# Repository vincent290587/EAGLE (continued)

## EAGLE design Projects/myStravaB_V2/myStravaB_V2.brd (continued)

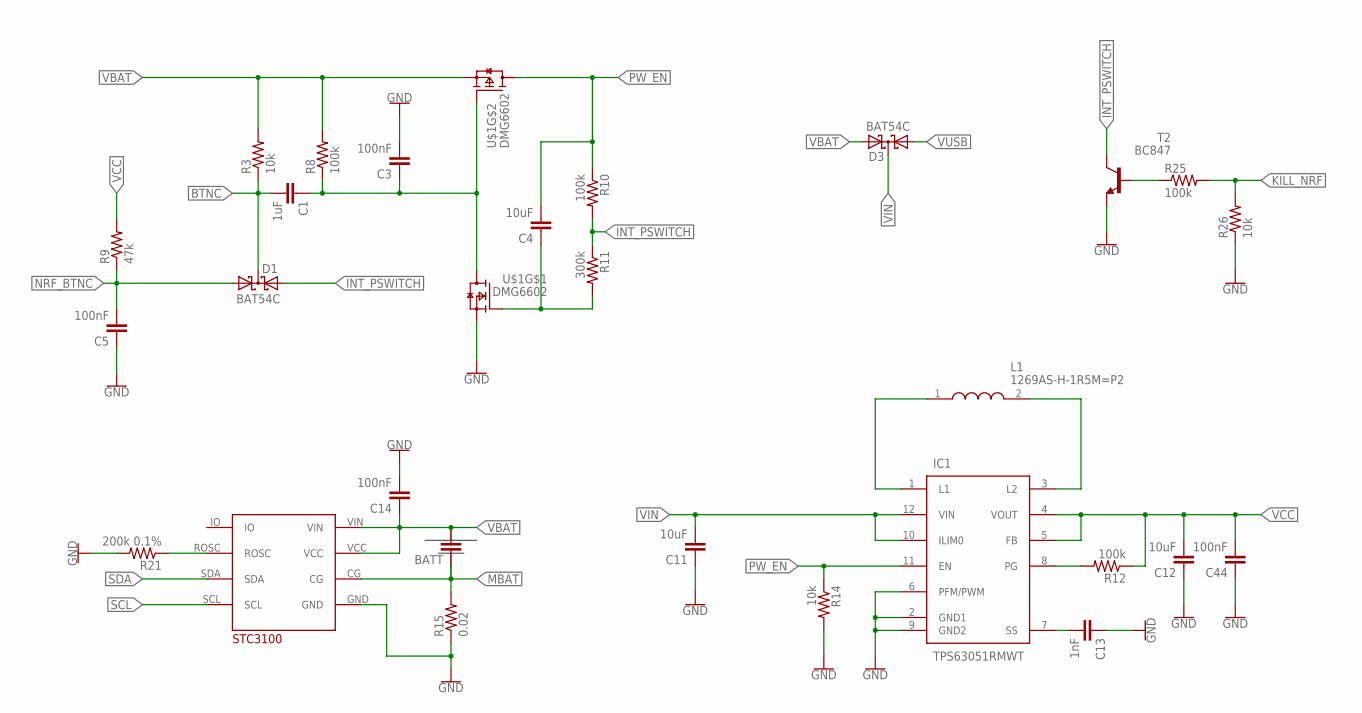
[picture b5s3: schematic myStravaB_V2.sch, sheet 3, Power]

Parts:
BATT: C-EUC1210; C1210
C1: 1uF; 0603
C3, C5: 100nF; 0603
C4: 10uF; 0603
C11: 10uF; C0805
C12: 10uF; C0603
C13: 1nF; C0603
C14, C44: 100nF; C0603
D1, D3: BAT54C; SOT23
IC1: TPS63051RMWT; QFN50P250X250X100-12N
L1: 1269AS-H-1R5M=P2; INDC2520X110N
R3, R14, R26: 10k; R0603
R8, R10, R12, R25: 100k; R0603
R9: 47k; R0603
R11: 300k; R0603
R15: 0.02; R0603
R21: 200k 0.1%; R0603
T2: BC847; SOT23
U$1: DMG6602; TSOT26
U$6: STC3100

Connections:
BTNC: C1.2, D1.3 (CC), R3.1; also elsewhere on the board
GND: C3.2, C5.1, C11.1, C12.1, C13.1, C14.2, C44.1, IC1.2 (GND1), IC1.6 (PFM/PWM), IC1.9 (GND2), R14.2, R15.1, R21.2, R26.1, T2.2 (E), U$1.P$5 (S), U$6.GND; also elsewhere on the board
INT_PSWITCH: D1.2 (A2), R10.2, R11.1, T2.3 (C)
KILL_NRF: R25.2, R26.2; also elsewhere on the board
L1: IC1.1 (L1), L1.1
L2: IC1.3 (L2), L1.2
MBAT: BATT.1, R15.2, U$6.CG
unnamed: C1.1, C3.1, R8.1, U$1.P$3 (G), U$1.P$6 (D)
unnamed: R25.1, T2.1 (B)
unnamed: C4.1, R11.2, U$1.P$1 (G)
NRF_BTNC: C5.2, D1.1 (A1), R9.1; also elsewhere on the board
PG: IC1.8 (PG), R12.2
PW_EN: C4.2, IC1.11 (EN), R10.1, R14.1, U$1.P$4 (D); also elsewhere on the board
ROSC: R21.1, U$6.ROSC
SCL: U$6.SCL; also elsewhere on the board
SDA: U$6.SDA; also elsewhere on the board
SS: C13.2, IC1.7 (SS)
VBAT: BATT.2, C14.1, D3.2 (A2), R3.2, R8.2, U$1.P$2 (S), U$6.VCC, U$6.VIN; also elsewhere on the board
VCC: C12.2, C44.2, IC1.4 (VOUT), IC1.5 (FB), R9.2, R12.1; also elsewhere on the board
VIN: C11.2, D3.3 (CC), IC1.10 (ILIM0), IC1.12 (VIN)
VUSB: D3.1 (A1); also elsewhere on the board

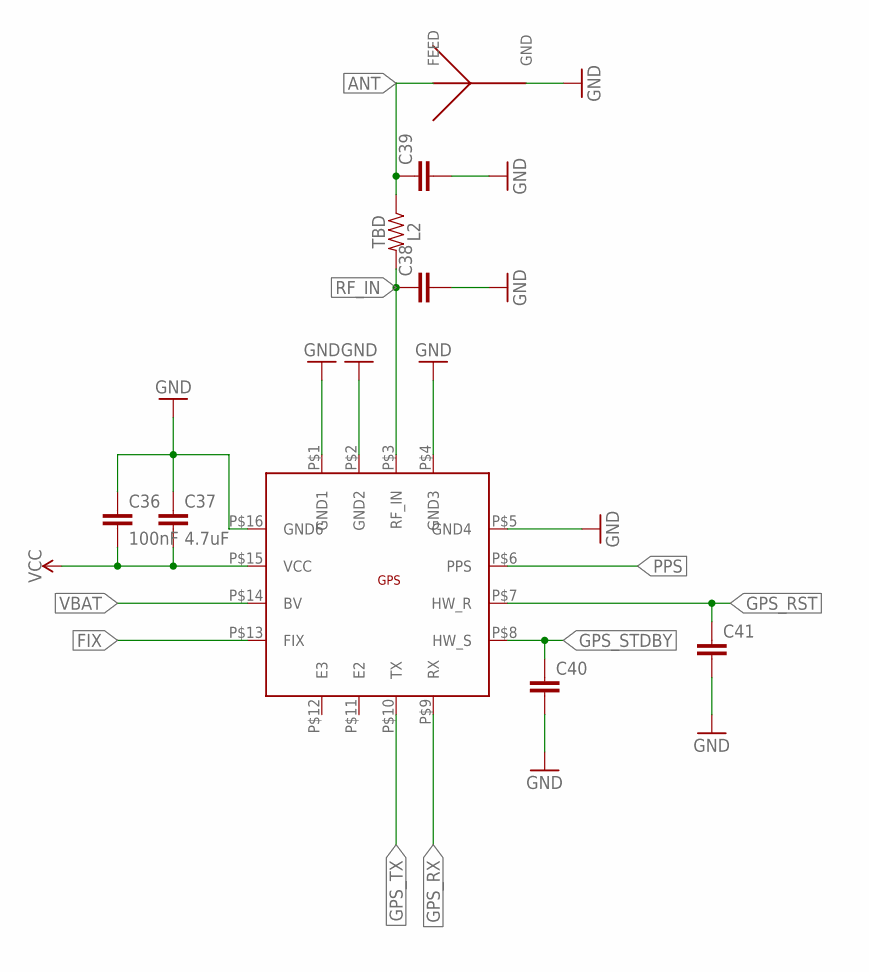
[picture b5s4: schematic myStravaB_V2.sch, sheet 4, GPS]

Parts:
C36: 100nF; C0603
C37: 4.7uF; C0603
C38, C39, C40, C41: C-EUC0603; C0603
L2: TBD; 0603
U$4: SR4G008
U$5: M10578

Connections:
ANT: C39.1, L2.1, U$4.P$2 (FEED)
FIX: U$5.P$13 (FIX); also elsewhere on the board
GND: C36.1, C37.1, C38.2, C39.2, C40.2, C41.2, U$4.P$3 (GND), U$4.P$4 (GND), U$4.P$6 (GND), U$5.P$1 (GND1), U$5.P$2 (GND2), U$5.P$4 (GND3), U$5.P$5 (GND4), U$5.P$16 (GND6); also elsewhere on the board
GPS_RST: C41.1, U$5.P$7 (HW_R); also elsewhere on the board
GPS_RX: U$5.P$9 (RX); also elsewhere on the board
GPS_STDBY: C40.1, U$5.P$8 (HW_S); also elsewhere on the board
GPS_TX: U$5.P$10 (TX); also elsewhere on the board
PPS: U$5.P$6 (PPS)
RF_IN: C38.1, L2.2, U$5.P$3 (RF_IN)
VBAT: U$5.P$14 (BV); also elsewhere on the board
VCC: C36.2, C37.2, U$5.P$15 (VCC); also elsewhere on the board

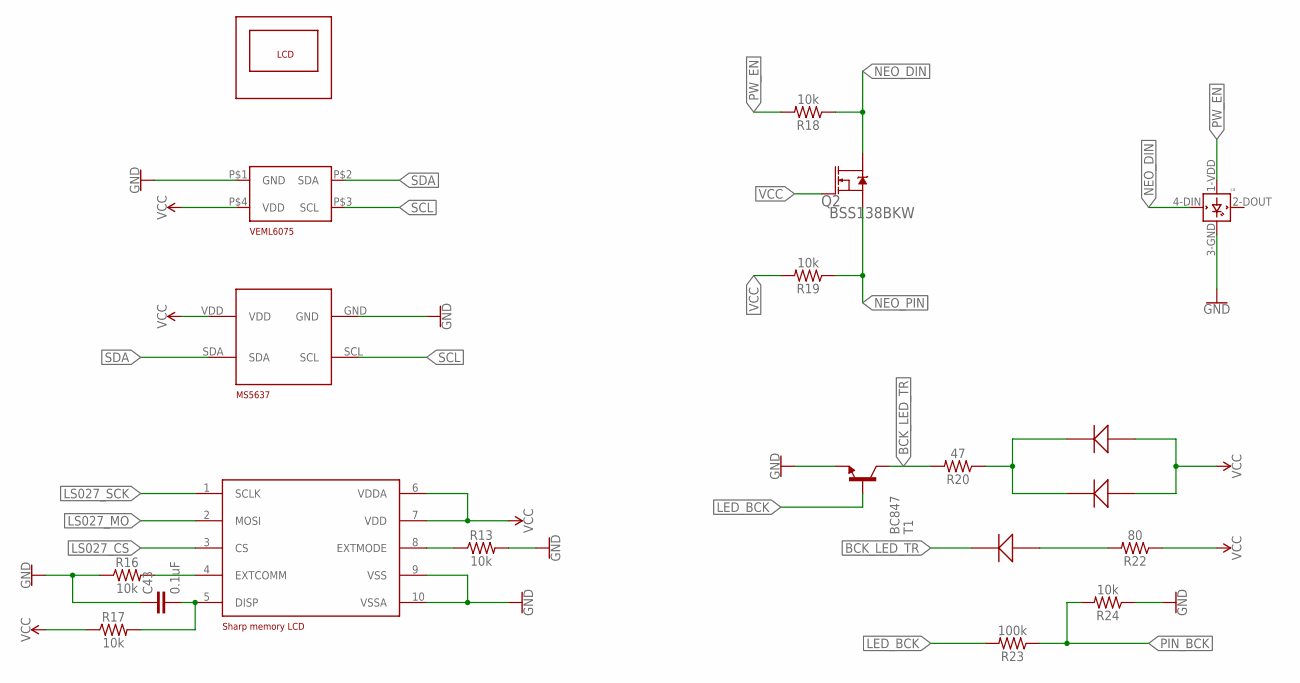
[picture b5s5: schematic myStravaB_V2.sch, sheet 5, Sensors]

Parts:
C43: 0.1uF; 0603
L4: WS2812B
MS1: MS5637
Q2: BSS138BKW; SOT65P210X110-3N
R13, R16, R17, R18, R19, R24: 10k; 0603
R20: 47; 0603
R22: 80; 0603
R23: 100k; 0603
T1: BC847; SOT23
U$14: VEML6075
U$15: SHARP27_FOOTPRINT; LCD27
U$16: SHARP27
U$17, U$18, U$19: KPA-2106SECK

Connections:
BCK_LED_TR: R20.2, T1.3 (C), U$19.P$1
DISP1: C43.2, R17.2, U$16.5 (DISP)
EXTCOMM1: R16.2, U$16.4 (EXTCOMM)
EXTMODE1: R13.1, U$16.8 (EXTMODE)
GND: C43.1, L4.3-GND (GND), MS1.GND, R13.2, R16.1, R24.1, T1.2 (E), U$14.P$1 (GND), U$16.9 (VSS), U$16.10 (VSSA); also elsewhere on the board
LED_BCK: R23.2, T1.1 (B)
LS027_CS: U$16.3 (CS); also elsewhere on the board
LS027_MO: U$16.2 (MOSI); also elsewhere on the board
LS027_SCK: U$16.1 (SCLK); also elsewhere on the board
unnamed: R22.2, U$19.P$2
unnamed: R20.1, U$17.P$1, U$18.P$1
NEO_DIN: L4.4-DIN (DIN), Q2.3 (D), R18.1
NEO_PIN: Q2.2 (S), R19.1; also elsewhere on the board
PIN_BCK: R23.1, R24.2
PW_EN: L4.1-VDD (VDD), R18.2; also elsewhere on the board
SCL: MS1.SCL, U$14.P$3 (SCL); also elsewhere on the board
SDA: MS1.SDA, U$14.P$2 (SDA); also elsewhere on the board
VCC: MS1.VDD, Q2.1 (G), R17.1, R19.2, R22.1, U$14.P$4 (VDD), U$16.6 (VDDA), U$16.7 (VDD), U$17.P$2, U$18.P$2; also elsewhere on the board

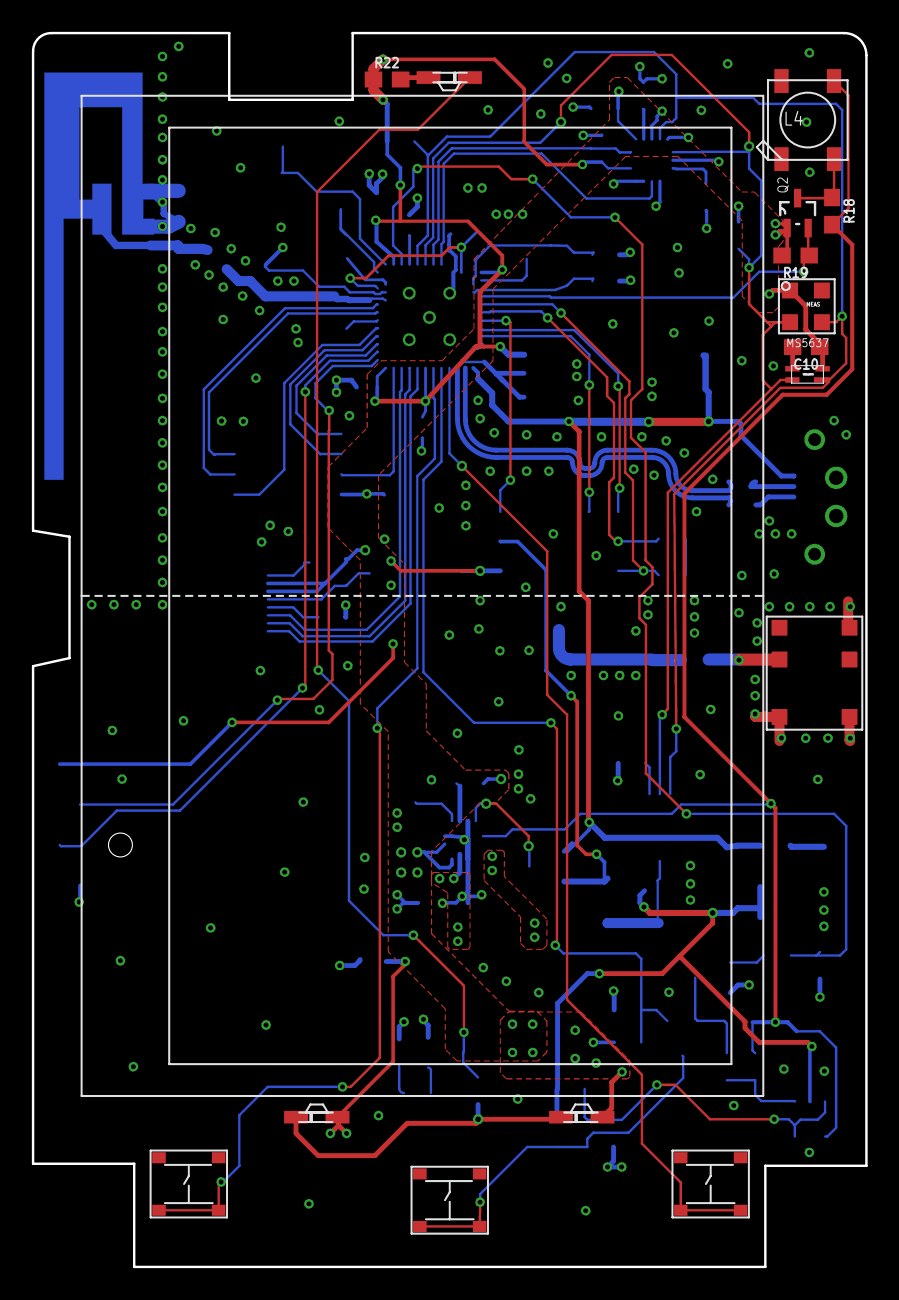
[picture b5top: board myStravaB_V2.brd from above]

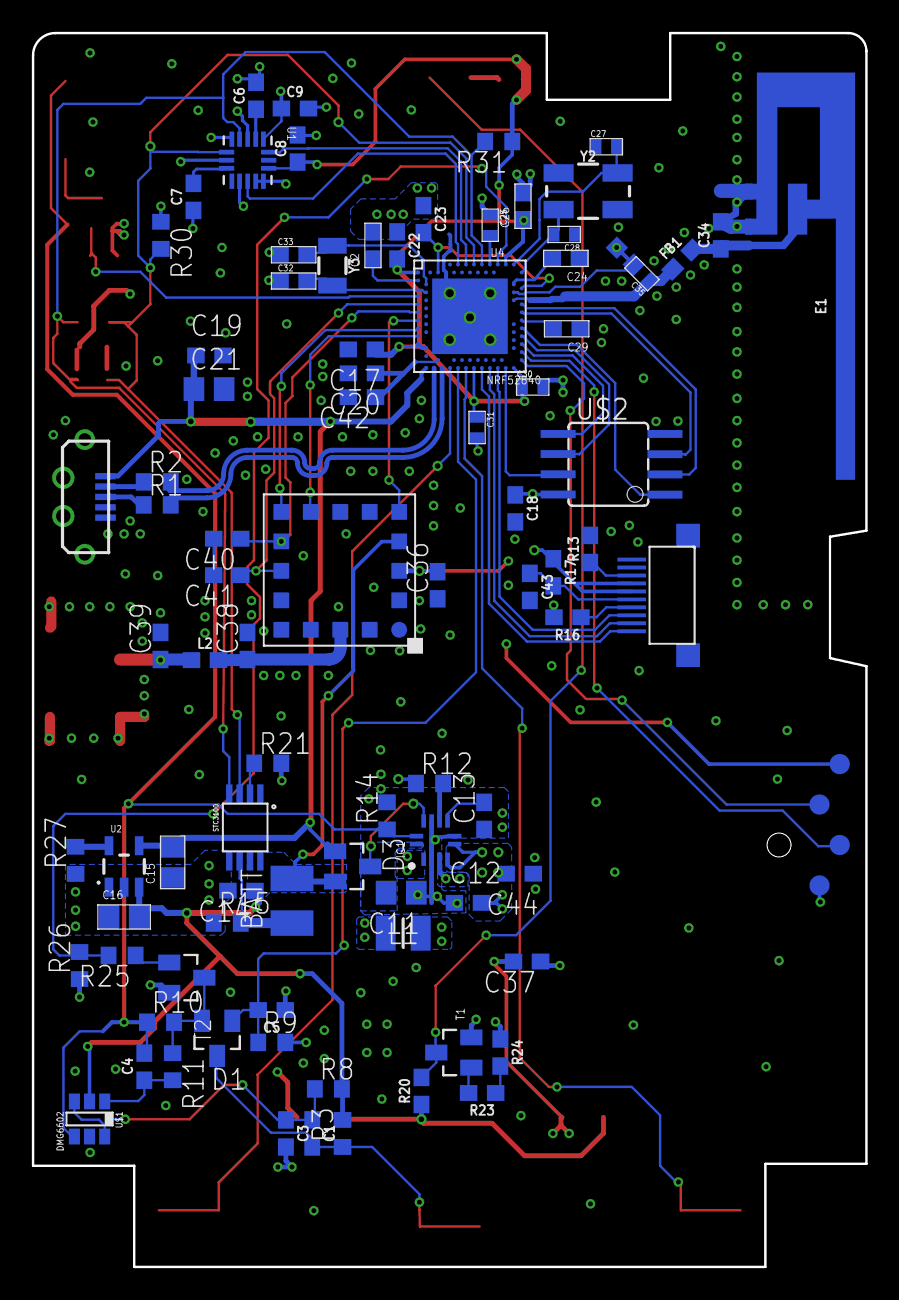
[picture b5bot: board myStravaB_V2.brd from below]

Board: 2 copper layers, 52.3 x 77.5 mm, 104 parts (88 on the bottom side), 73 nets.

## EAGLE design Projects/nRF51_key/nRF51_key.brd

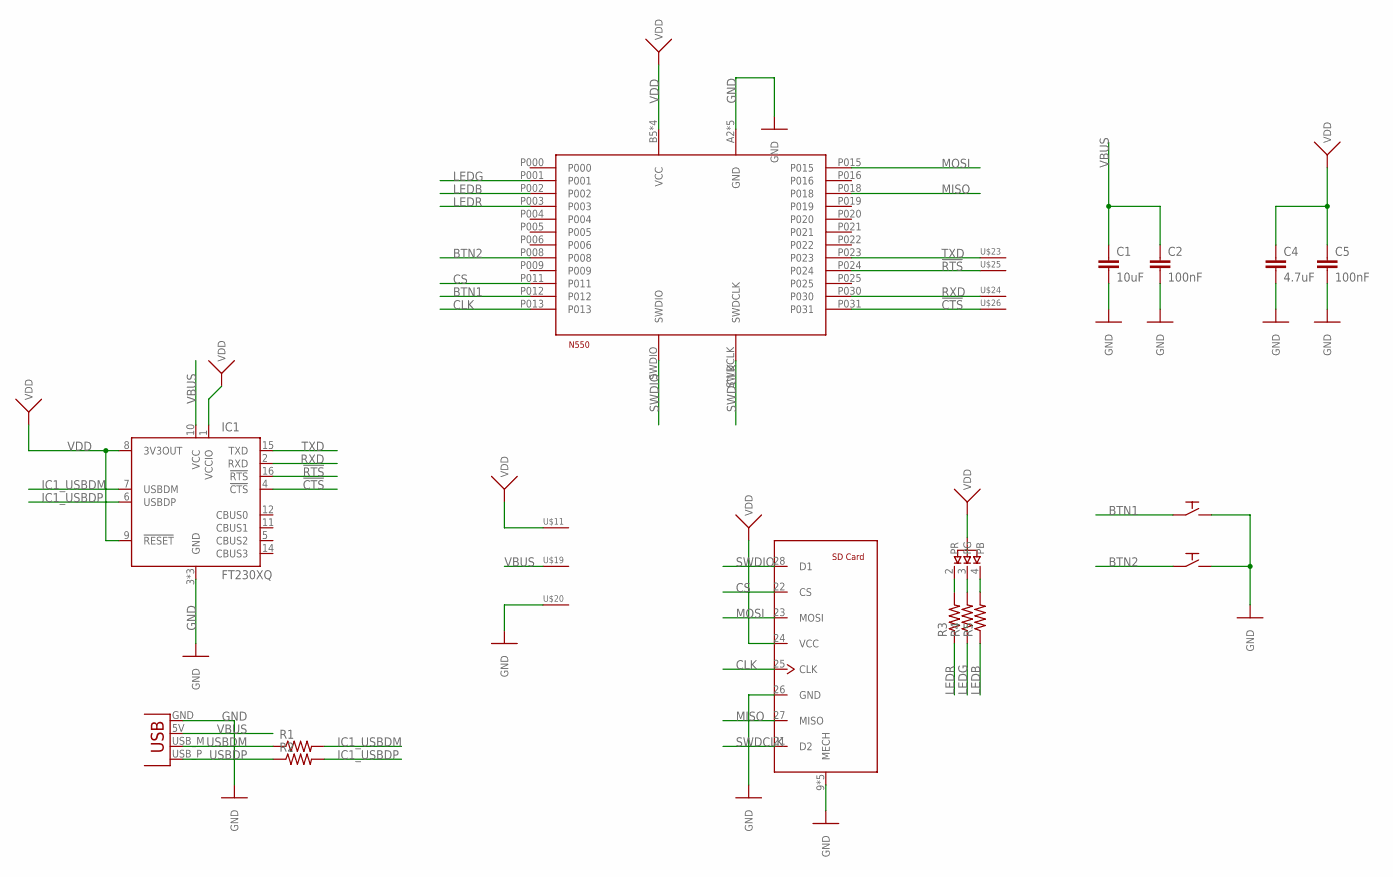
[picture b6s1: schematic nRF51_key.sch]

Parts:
C1: 10uF; C0603
C2, C5: 100nF; C0603
C4: 4.7uF; C0603
D1: LRTBR48G; LRTBR48GP9Q71R7S526NP68
IC1: FT230XQ; QFN16
J1: 47571-0001
R1, R2, R3, R4, R5: RESISTOR0603; R0603
SPST1, SPST2: PTS526SK08; PTS526SKG15SMTR2LFS
U$1: N550
U$11, U$19, U$20, U$23, U$24, U$25, U$26: PAD; PAD_0.8
X1: USBPCB; USB-A-PCB

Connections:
!CTS: IC1.4 (!CTS), U$1.P031, U$26.PAD
!RTS: IC1.16 (!RTS), U$1.P024, U$25.PAD
BTN1: SPST1.1, SPST1.2, U$1.P012
BTN2: SPST2.1, SPST2.2, U$1.P008
CLK: J1.25 (CLK), U$1.P013
CS: J1.22 (CS), U$1.P011
GND: C1.2, C2.2, C4.2, C5.2, IC1.3 (GND), IC1.13 (GND), IC1.EXP (GND), J1.9 (MECH), J1.10 (MECH), J1.11 (MECH), J1.12 (MECH), J1.13 (MECH), J1.26 (GND), SPST1.3, SPST1.4, SPST2.3, SPST2.4, U$1.A2 (GND), U$1.A3 (GND), U$1.A4 (GND), U$1.A5 (GND), U$1.A6 (GND), U$20.PAD, X1.GND
IC1_USBDM: IC1.7 (USBDM), R1.2
IC1_USBDP: IC1.6 (USBDP), R2.2
LEDB: R5.1, U$1.P002
LEDG: R4.1, U$1.P001
LEDR: R3.1, U$1.P003
MISO: J1.27 (MISO), U$1.P018
MOSI: J1.23 (MOSI), U$1.P015
unnamed: D1.2 (PR), R3.2
unnamed: D1.3 (PG), R4.2
unnamed: D1.4 (PB), R5.2
RXD: IC1.2 (RXD), U$1.P030, U$24.PAD
SWDCLK: J1.21 (D2), U$1.SWDCLK
SWDIO: J1.28 (D1), U$1.SWDIO
TXD: IC1.15 (TXD), U$1.P023, U$23.PAD
USBDM: R1.1, X1.USB_M (D-)
USBDP: R2.1, X1.USB_P (D+)
VBUS: C1.1, C2.1, IC1.10 (VCC), U$19.PAD, X1.5V (VBUS)
VDD: C4.1, C5.1, D1.1, IC1.1 (VCCIO), IC1.8 (3V3OUT), IC1.9 (!RESET), J1.24 (VCC), U$1.B5 (VCC), U$1.B6 (VCC), U$1.C5 (VCC), U$1.C6 (VCC), U$11.PAD

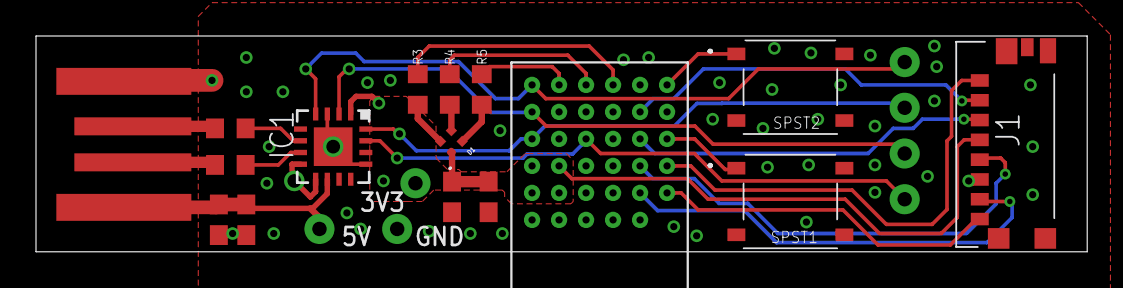
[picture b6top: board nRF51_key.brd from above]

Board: 2 copper layers, 58.4 x 12.0 mm, 23 parts (0 on the bottom side), 25 nets.
